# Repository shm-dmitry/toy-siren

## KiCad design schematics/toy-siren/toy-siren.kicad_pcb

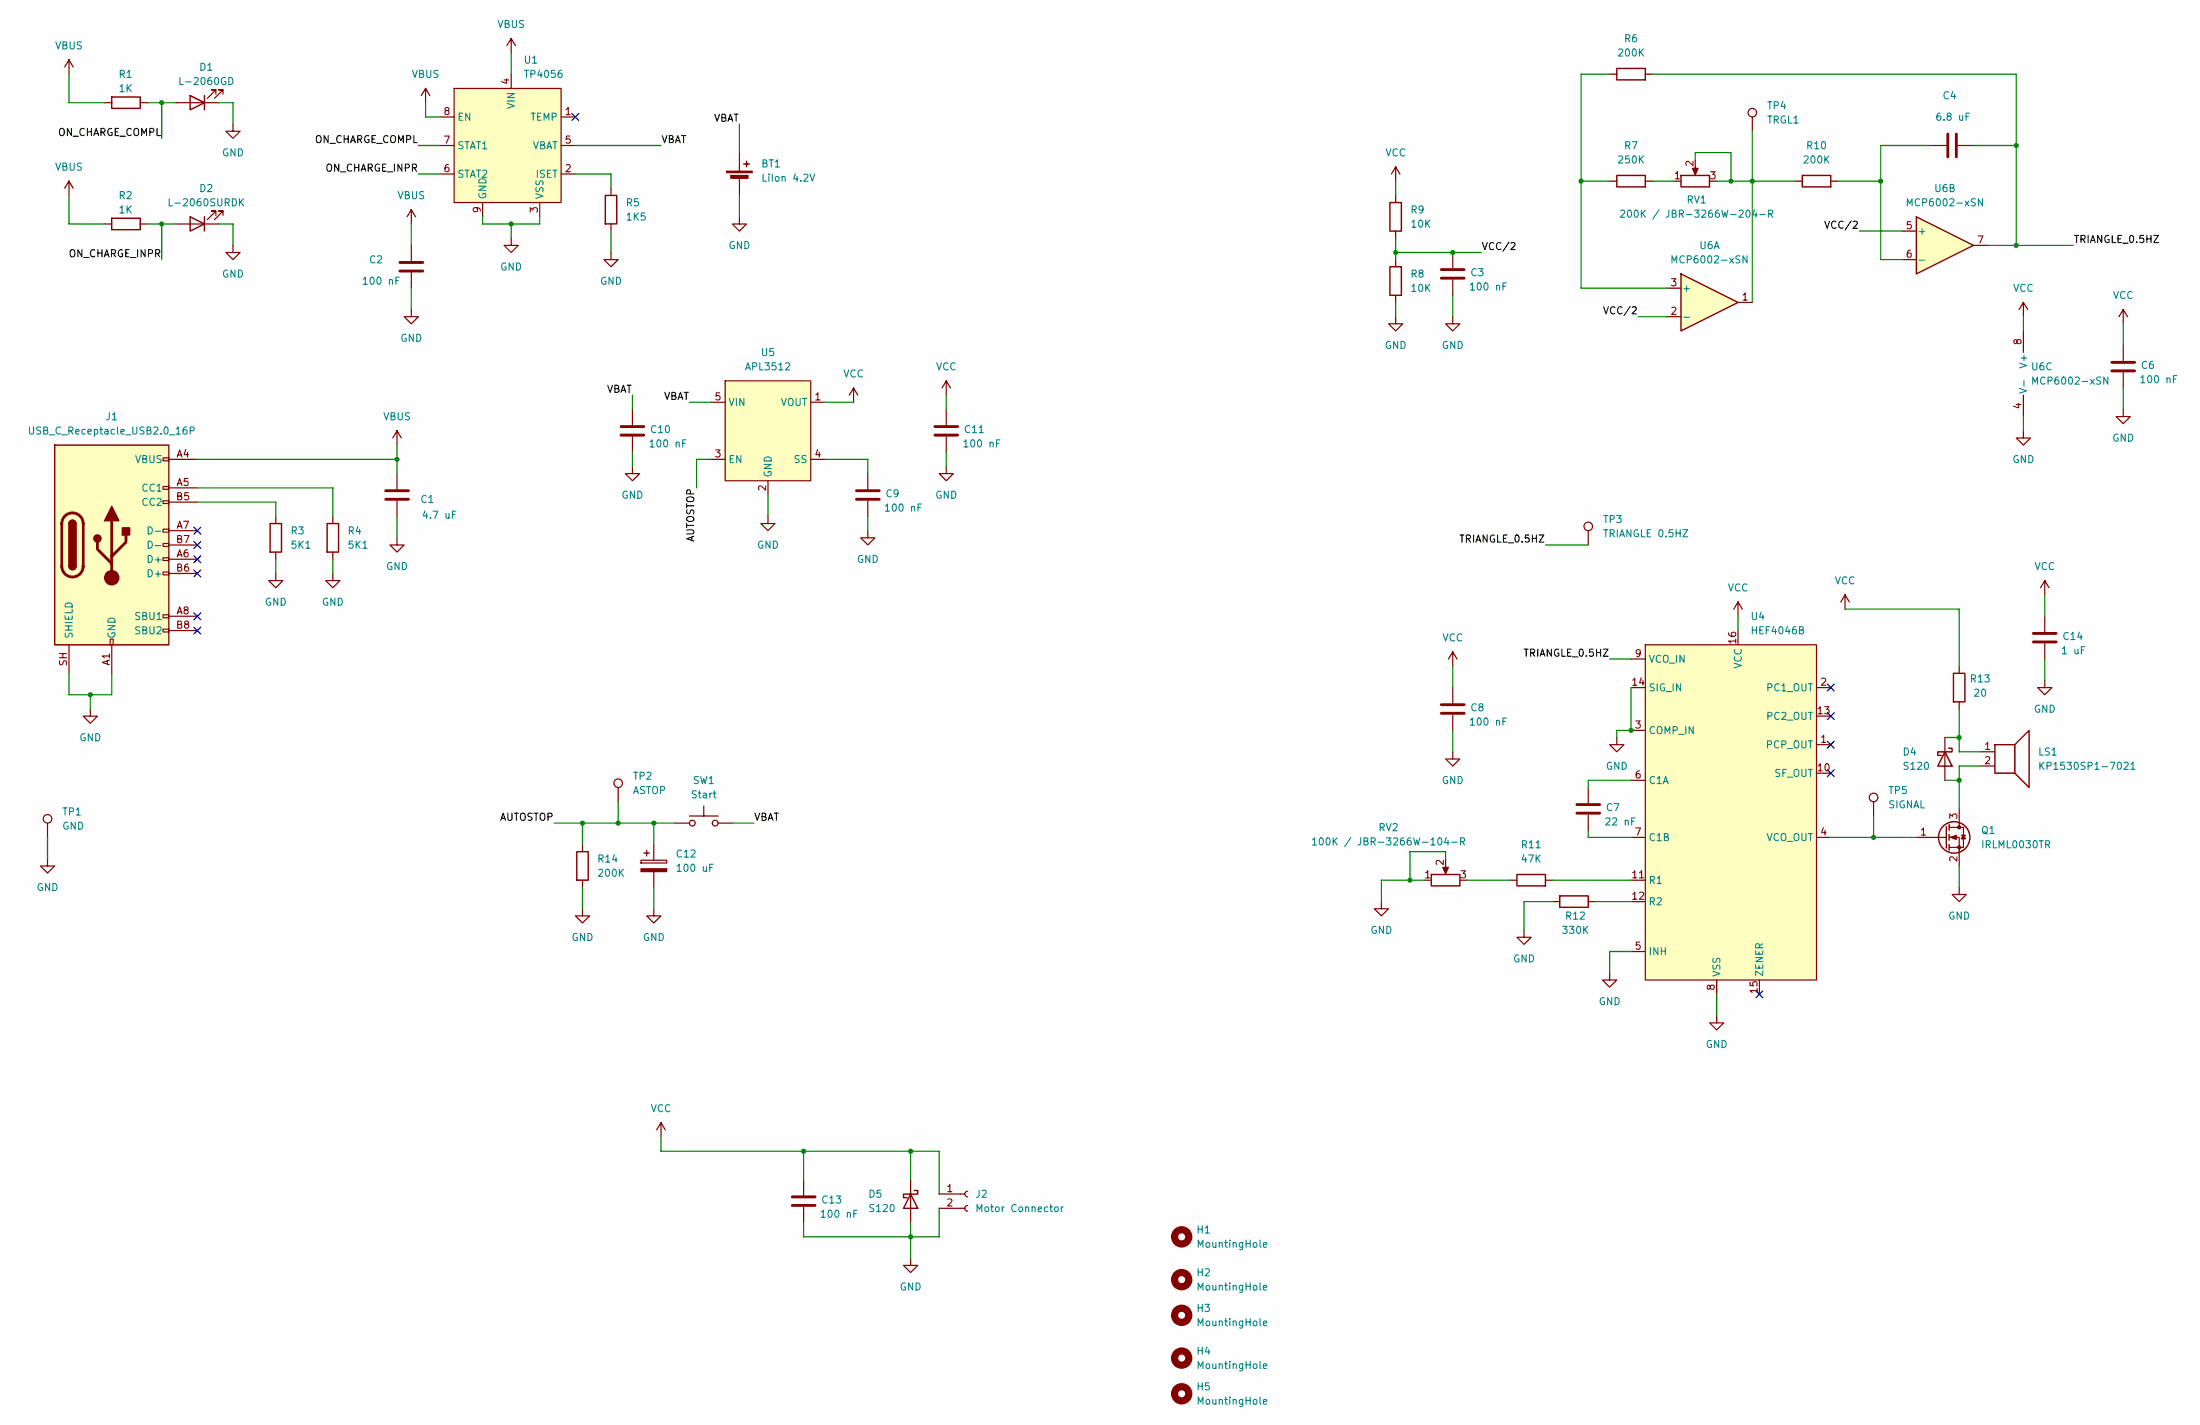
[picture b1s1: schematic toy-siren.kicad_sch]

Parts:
BT1: LiIon 4.2V; JST_XH_B2B-XH-A_1x02_P2.50mm_Vertical
C1: 4.7 uF; C_0603_1608Metric
C2, C3, C6, C8, C9, C10, C11, C13: 100 nF; C_0603_1608Metric
C4: 6.8 uF; C_0603_1608Metric
C7: 22 nF; C_0603_1608Metric
C12: 100 uF; CP_EIA-7343-20_Kemet-V_HandSolder
C14: 1 uF; C_0603_1608Metric
D1: L-2060GD; LED_D1.8mm_W3.3mm_H2.4mm
D2: L-2060SURDK; LED_D1.8mm_W3.3mm_H2.4mm
D4, D5: S120; D_SOD-123
H1, H2, H3, H4, H5: MountingHole; MountingHole_2.2mm_M2
J1: USB_C_Receptacle_USB2.0_16P; USB_C_P16_MIDMOUNT_1.6
J2: Motor Connector; JST_XH_B2B-XH-A_1x02_P2.50mm_Vertical
LS1: KP1530SP1-7021; JST_XH_B2B-XH-A_1x02_P2.50mm_Vertical
Q1: IRLML0030TR; SOT-23
R1, R2: 1K; R_0805_2012Metric_Pad1.20x1.40mm_HandSolder
R3, R4: 5K1; R_0805_2012Metric_Pad1.20x1.40mm_HandSolder
R5: 1K5; R_0805_2012Metric_Pad1.20x1.40mm_HandSolder
R6, R10, R14: 200K; R_0805_2012Metric_Pad1.20x1.40mm_HandSolder
R7: 250K; R_0805_2012Metric_Pad1.20x1.40mm_HandSolder
R8, R9: 10K; R_0805_2012Metric_Pad1.20x1.40mm_HandSolder
R11: 47K; R_0805_2012Metric_Pad1.20x1.40mm_HandSolder
R12: 330K; R_0805_2012Metric_Pad1.20x1.40mm_HandSolder
R13: 20; R_0805_2012Metric_Pad1.20x1.40mm_HandSolder
RV1: 200K / JBR-3266W-204-R; Potentiometer_Bourns_3266W_Vertical
RV2: 100K / JBR-3266W-104-R; Potentiometer_Bourns_3266W_Vertical
SW1: Start; JST_XH_B2B-XH-A_1x02_P2.50mm_Vertical
TP1: GND; TestPoint_THTPad_3.0x3.0mm_Drill1.5mm
TP2: ASTOP; TestPoint_Pad_D2.5mm
TP3: TRIANGLE 0.5HZ; TestPoint_Pad_D2.5mm
TP4: TRGL1; TestPoint_Pad_D2.5mm
TP5: SIGNAL; TestPoint_Pad_D2.5mm
U1: TP4056; SOP127P600X175-9N
U4: HEF4046B; SO-16_3.9x9.9mm_P1.27mm
U5: APL3512; SOT-23-5_HandSoldering
U6: MCP6002-xSN; SOIC-8_3.9x4.9mm_P1.27mm

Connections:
/AUTOSTOP: C12.1, R14.1, SW1.1, TP2.1 (1_1), U5.3 (EN)
/ON_CHARGE_COMPL: D1.2 (A), R1.1, U1.7 (STAT1)
/ON_CHARGE_INPR: D2.2 (A), R2.1, U1.6 (STAT2)
/TRIANGLE_0.5HZ: C4.2, R6.2, TP3.1 (1_1), U4.9 (VCO_IN), U6.7
/VBAT: BT1.1 (+), C10.1, SW1.2, U1.5 (VBAT), U5.5 (VIN)
/VCC/2: C3.1, R8.2, R9.1, U6.2 (-), U6.5 (+)
GND: BT1.2 (-), C1.2, C2.2, C3.2, C6.2, C8.2, C9.2, C10.2, C11.2, C12.2, C13.2, C14.2, D1.1 (K), D2.1 (K), D5.2 (A), J1.A1 (GND), J1.A12 (GND), J1.B1 (GND), J1.B12 (GND), J1.SH (SHIELD), J2.2, Q1.2 (S), R3.2, R4.2, R5.2, R8.1, R12.2, R14.2, RV2.1, RV2.2, TP1.1 (1_1), U1.3 (VSS), U1.9 (GND), U4.3 (COMP_IN), U4.5 (INH), U4.8 (VSS), U4.14 (SIG_IN), U5.2 (GND), U6.4 (V-)
unnamed: D4.2 (A), LS1.2, Q1.3 (D)
unnamed: D4.1 (K), LS1.1, R13.2
unnamed: J1.A5 (CC1), R4.1
unnamed: J1.B5 (CC2), R3.1
unnamed: Q1.1 (G), TP5.1 (1_1), U4.4 (VCO_OUT)
unnamed: R7.2, RV1.1
unnamed: R10.1, RV1.2, RV1.3, TP4.1 (1_1), U6.1
unnamed: R11.1, RV2.3
unnamed: R5.1, U1.2 (ISET)
unnamed: C7.1, U4.6 (C1A)
unnamed: C7.2, U4.7 (C1B)
unnamed: R11.2, U4.11 (R1)
unnamed: R12.1, U4.12 (R2)
unnamed: C9.1, U5.4 (SS)
unnamed: R6.1, R7.1, U6.3 (+)
unnamed: C4.1, R10.2, U6.6 (-)
VBUS: C1.1, C2.1, J1.A4 (VBUS), J1.A9 (VBUS), J1.B4 (VBUS), J1.B9 (VBUS), R1.2, R2.2, U1.4 (VIN), U1.8 (EN)
VCC: C6.1, C8.1, C11.1, C13.1, C14.1, D5.1 (K), J2.1, R9.2, R13.1, U4.16 (VCC), U5.1 (VOUT), U6.8 (V+)

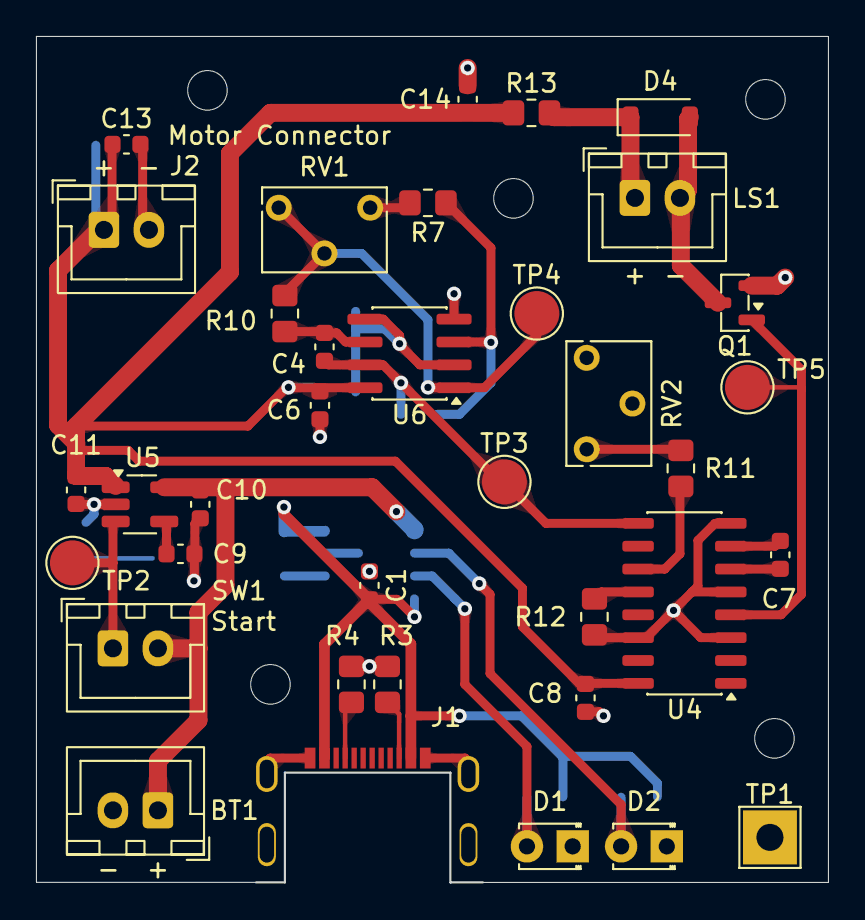
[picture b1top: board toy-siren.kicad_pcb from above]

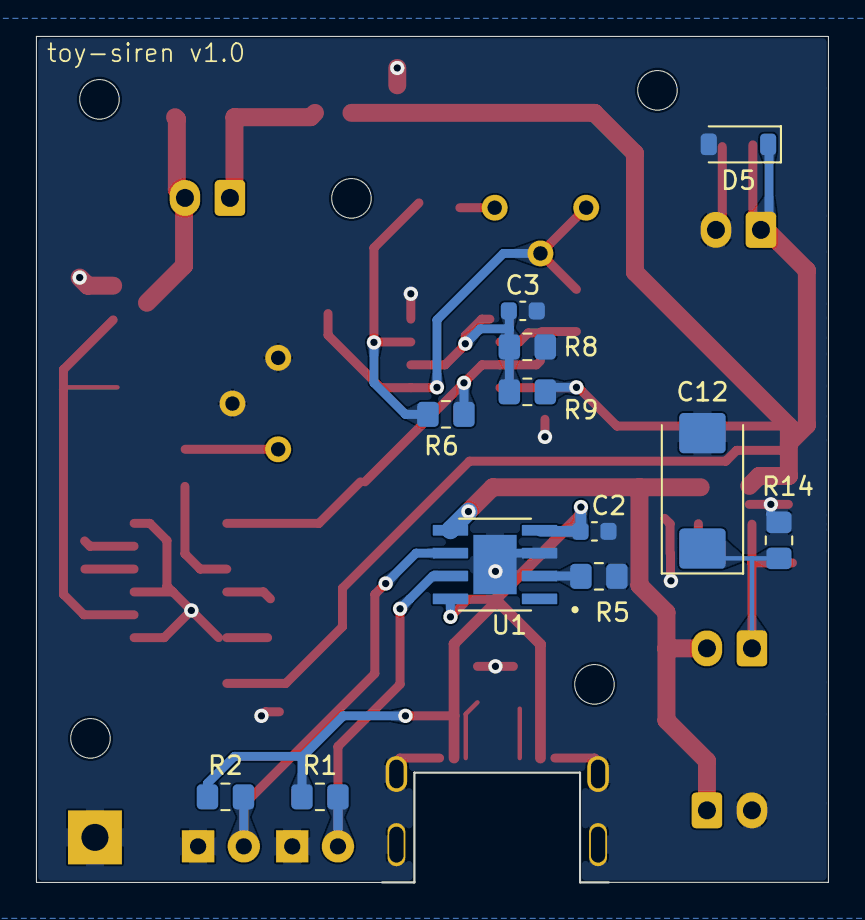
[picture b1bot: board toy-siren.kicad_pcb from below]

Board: 2 copper layers, 44.0 x 47.0 mm, 53 parts (12 on the bottom side), 25 nets.
